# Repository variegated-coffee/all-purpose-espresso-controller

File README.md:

# All Purpose Espresso Controller

Espresso electronics are usually proprietary affairs with little to no expandability. The purpose of this project is to give everyone an open source alternative with lots of features and flexibility. 

It is designed to be useful in many different espresso machines, and for many different hardware configurations. It has the same PCB size as many very common Gicar controllers, making it fairly easy to swap this board into your existing enclosure. It also comes with screw holes, so a 3D printed enclosure is another option.

There's also a [corresponding 100-240 VAC board](https://github.com/open-lcc/all-purpose-espresso-controller-hv-board), with relays and an AC/DC converter, designed to also fit into those same Gicar enclosures.

## High-level features

* RP2040 microcontroller with 2 MB of program flash, and 2 MB of settings flash
* ESP32-S3 for extra processing power and Wi-fi/Bluetooth connectivity
* SD card reader
* Plenty of IO, at 12V, 5V and 3V3 levels
* Dedicated connector for a UART based user interface device, like an [Open LCC](https://github.com/open-lcc/open-lcc-board) or a Nextion touchscreen (selectable 5V or 3V3 level)
* EyeSPI connector for ESP32-S3
* ADS124S08 ADC (intended for e.g. pressure transducers or NTCs)
* FDC1004 Capacitance-to-digital (inteded for e.g. water level probes or capitance based controls)
* QWIIC ports (one per microcontroller) for additional expandability

[IBOM](https://raw.githack.com/open-lcc/all-purpose-espresso-controller/r0d/manufacturing-data/r0d/ibom.html)

## Project status

The current hardware revision is R0D. It hasn't been manufactured yet, and you shouldn't be the first one to do it.

## Disclaimer

Anything you do with this, you do at your own risk. This hardware hasn't even been manufactured by it's creator yet. Your machine uses both line voltage power, high pressured hot water, steam and other dangerous components. You *really* shouldn't be using this yet; in fact, you shouldn't even consider it. Risks include but are not limited to, damaging your machine, personal injury, property damage and summoning dead Cthulhu from his sleep at R'lyeh.

## Connectivity
* CN1 - Display Connector, either for Open LCC or a Nextion Display
  * UART (selectable 3V3 or 5V, default 3V3)
    * JP9 selects voltage
    * RP2040 UART0
    * ESP32 GPIO17/GPIO14
  * 1x 12V output (SR2 DRAIN6)
  * 1x 3V3 output (SR2 DRAIN7)
  * 1 3V3/5V pin and GND pin
* CN2 - HV Board Connector
  * 12V and GND
  * 4 Open drains (SR1 DRAIN0-3)
* CN3 - Separate PSU Connector
  * 12V and GND
* CN4 - Capacitive sense connector
* CN5 - ADC port
  * See note below
* CN6 - ADC port
  * See note below
* CN7 - ADC port
  * See note below
* CN8 - Outputs
  * 4x 5V/12V Outputs
    * Voltage selectable by JP4-6/JP16
  * GND
* CN9 - Open drains and 3V3 IO
  * 3x Open drains (SR1 DRAIN5-7)
  * 3x 3V3 IO (RP2040 GPIO12-14)
  * 12V/GND
* CN10 - Open drain
  * SR2 DRAIN1
  * 12V
* CN11 - Open drain
  * SR2 DRAIN0
  * 12V
* CN12 - 3V3/5V GPIO
  * RP2040 GPIO22
  * Shifted through MOSFET level shifter
  * Can be switched to a 500 mA output with solder jumper
  * GND
* CN13 - 3V3/5V GPIO
  * RP2040 GPIO23
  * Shifted through MOSFET level shifter
  * Can be switched to a 500 mA output with solder jumper
  * GND
* CN14 - GPIO
  * RP2040 GPIO18-21
    * GP19 can be connected to SD Card Detect via a solder jumper
    * GP21 is also connected to an LED
  * RP2040 GPIO26-29
    * ADC Capable

### ADC
By default, CN5 and CN6 are configured for a ratiometric measurement. In order to use it as such, you need to fit a reference resistor for REF0. The reference resistor needs to be larger than the measured values (e.g. for a PT100, use a 400 ohm resistor), and needs to be high accuracy and low drift. 

AIN1-2, AIN4-7, and AIN9-10 are all outfitted with RC filters, as is REF0. The board is also designed in such a way that you can, by sacrificing an RC filter, convert a channel to instead use an upstream resistor divider. 

The ADS124S08 features two external references (REF0 and REF1), as well as an internal 2.5V reference. AIN6-7 double as REFP1/REFN1. The board is designed with footprints for a reference resistor.

#### Common configurations

##### PT100 RTD

##### PT1000 RTD

##### 50k NTC - Ratiometric

##### 50k NTC - Resistor divider

##### 0.3 – 4.5 V Pressure trandducer - 5 V Reference

##### 0.3 – 4.5 V Pressure trandducer - Resistor divider

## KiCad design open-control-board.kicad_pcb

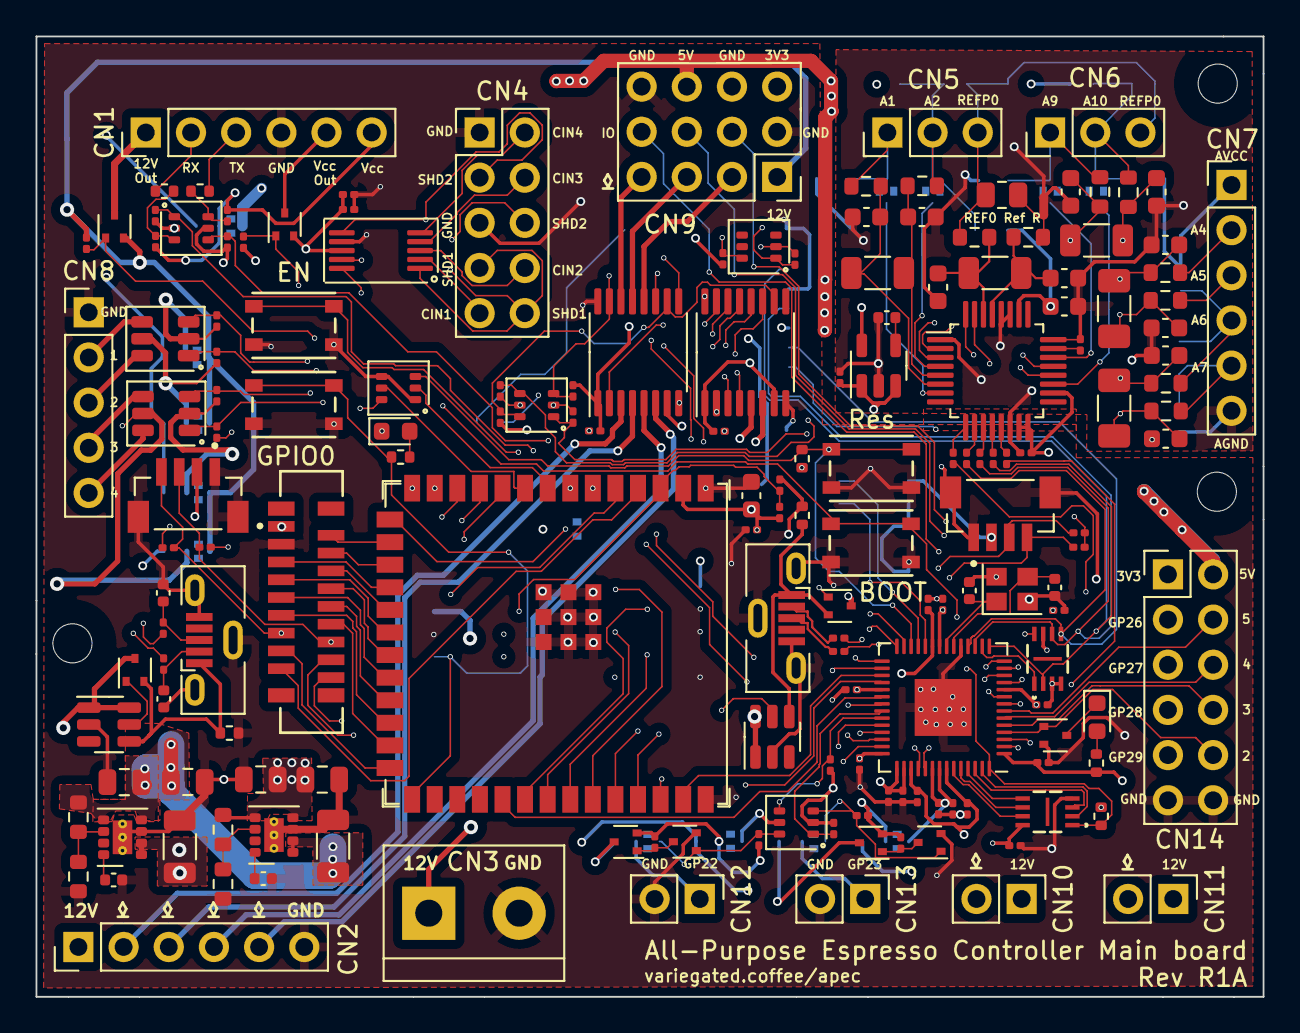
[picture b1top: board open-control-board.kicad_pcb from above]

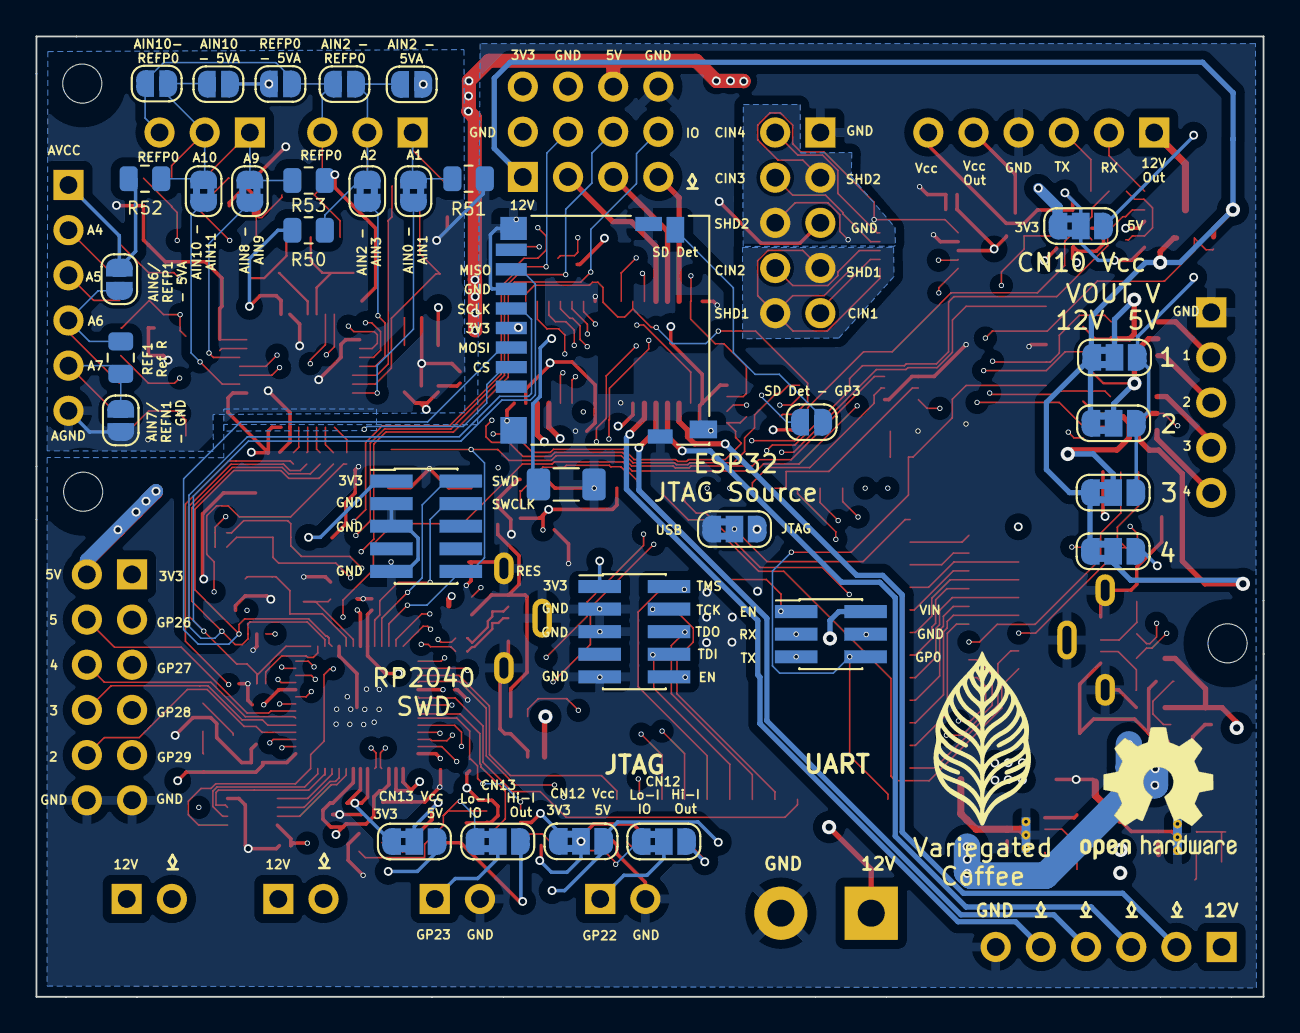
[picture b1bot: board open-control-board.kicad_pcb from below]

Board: 6 copper layers, 69.0 x 54.0 mm, 203 parts (32 on the bottom side), 175 nets.

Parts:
C1, C5, C48: 6.8 nF, 50V; C_0402_1005Metric
C2, C6: 10 μF, 25 V, X7R; C_1206_3216Metric
C3, C28, C36: 51 nF, C0G; C_1206_3216Metric
C4, C8, C49, C50: 22 uF, 10V, X7T; C_0805_2012Metric
C7, C26, C29, C35, C37, C38, C40, C41, C43, C44: 5.1 nF, C0G; C_0603_1608Metric
C9, C10: 12 pF; C_0402_1005Metric
C11, C22, C25, C30, C47, C51: 1 uF, >6.3V, X5R; C_0201_0603Metric
C12, C13, C14, C15, C16, C17, C18, C19, C20, C21, C23, C24, C27, C31, C45, C53, C54: 100 nF, >10V, X6S; C_0201_0603Metric
C32: 22 uF, 6.3V, X5R; C_0603_1608Metric
C33, C34: NC; C_0402_1005Metric
C39, C42: C_Small; C_1206_3216Metric_Pad1.33x1.80mm_HandSolder
C46: 330 nF; C_0603_1608Metric
C52: 47 uF; C_1206_3216Metric_Pad1.33x1.80mm_HandSolder
CN1: LCC Port; PinHeader_1x06_P2.54mm_Vertical
CN2, CN7: Conn_01x06_Pin; PinHeader_1x06_P2.54mm_Vertical
CN3: 12V Separate Supply; TerminalBlock_bornier-2_P5.08mm
CN4: Conn_02x05_Counter_Clockwise; PinHeader_2x05_P2.54mm_Vertical
CN5: NTC Brew Boiler; PinHeader_1x03_P2.54mm_Vertical
CN6: NTC Service Boiler; PinHeader_1x03_P2.54mm_Vertical
CN8: Conn_01x05_Pin; PinHeader_1x05_P2.54mm_Vertical
CN9: Conn_3x04
CN10, CN11, CN12, CN13: PinHeader_1x02_P2.54mm_Vertical
CN14: Conn_02x06_Odd_Even; PinHeader_2x06_P2.54mm_Vertical
D1, D2: KT-0603W; LED_0603_1608Metric
H1, H2, H3: MountingHole; MountingHole_2.2mm_M2
J1, J16: USB_B_Micro; USB_Micro-B_Molex-105133-0001
J2, J17: BM04B-SRSS-TB(LF)(SN); JST_BM04B-SRSS-TB(LF)(SN)
J3: Conn_02x03_Odd_Even; PinHeader_2x03_P1.27mm_Vertical_SMD
J4: Molex_0525591853; CON_525591853_MOL
J5: Micro_SD_Card_Det_Hirose_DM3AT; microSD_HC_Hirose_DM3D-SF
J13, J15: Conn_02x05_Odd_Even; PinHeader_2x05_P1.27mm_Vertical_SMD
JP1, JP2, JP3, JP7, JP10, JP15, JP22, JP23: SolderJumper_2_Open; SolderJumper-2_P1.3mm_Open_RoundedPad1.0x1.5mm
JP4, JP5, JP6, JP8, JP9, JP16, JP18, JP19, JP24, JP25: SolderJumper_3_Bridged12; SolderJumper-3_P1.3mm_Bridged2Bar12_RoundedPad1.0x1.5mm_Num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
JP13, JP17, JP20, JP21: SolderJumper_2_Bridged; SolderJumper-2_P1.3mm_Bridged2Bar_RoundedPad1.0x1.5mm
NT1: NetTie_2; NetTie-2_SMD_Pad0.5mm
Q1, Q2, Q8, Q15: DMP21D0UT-7; SOT-523
Q3, Q5: Q_PMOS-E_DUAL_Generic_SEP_S1G1D2S2G2D1; TSOT-23-6
Q4, Q6, Q7, Q11, Q12: DMN63D8LDW; SOT-363_SC-70-6
Q9, Q10, Q13, Q14, Q16: DMG1012T-7; SOT-523
R1, R2, R19, R22, R23, R28, R29, R30, R34, R36, R37, R38, R39, R40, R41, R42, R43, R59, R61, R62, R63, R64, R65, R67, R68, R69, R70: 10K; R_0201_0603Metric
R3, R13: 18K7; R_0402_1005Metric
R4, R50, R51, R52, R53, R66: R_Small; R_0805_2012Metric
R5, R6: 1K; R_0402_1005Metric
R7: 71K5; R_0603_1608Metric
R8: 13K3; R_0603_1608Metric
R9: 75K; R_0603_1608Metric
R10: 24K; R_0603_1608Metric
R11, R12: 27R; R_0201_0603Metric
R14, R15, R21, R24, R25, R26, R27, R35: 6K04 1%; R_0603_1608Metric
R16, R20: 4K99 1%; R_0603_1608Metric
R17, R18: 4K7; R_0402_1005Metric
R31, R44: 120R; R_0402_1005Metric
R32, R33: 0R; R_0201_0603Metric
R45, R46, R47, R48, R49: 47R; R_0201_0603Metric
SW1, SW2, SW3, SW4: SW_Push; SW4_PTS815 SJM 250 SMTR LFS_CNK
U1, U3: TPS82130; Texas_SIL0008D_MicroSiP-8-1EP_2.8x3mm_P0.65mm_EP1.1x1.9mm_T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
U2, U9: W25Q16JVUXIQ; W25Q16JVUXIQ_WIN
U4: RP2040; QFN-56-1EP_7x7mm_P0.4mm_EP3.2x3.2mm
U5: ESP32-S3-WROOM-1; ESP32-S3-WROOM-1U
U6: ADS124S08IPBSR; LQFP-32_5x5mm_P0.5mm
U7, U8: LM5050-1; TSOT-23-6
U10: FDC1004; VSSOP-10_3x3mm_P0.5mm
U11: TC2014-5.0VxCTTR; SOT-23-5
U15, U16: STPIC6C595TTR; TSSOP-16_4.4x5mm_P0.65mm
Y1: XYDBPCNANF-12MHZ; Crystal_SMD_2520-4Pin_2.5x2.0mm

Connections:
+3V3: C8.1, C14.2, C15.2, C16.2, C17.2, C18.2, C19.2, C20.1, C21.1, C22.1, C23.2, C24.1, C25.1, C27.2, C31.2, C32.2, C45.1, C50.1, C52.1, CN9.9, CN14.1, J2.2, J4.1 (Vcc), J5.4 (VDD), J13.1, J15.1, J17.2, JP8.3 (B), JP9.1 (A), JP19.1 (A), JP24.1 (A), Q1.2 (S), Q4.2 (G1), Q4.5 (G2), Q6.2 (G1), Q11.2 (G1), Q11.5 (G2), Q12.2 (G1), Q12.5 (G2), R1.1, R9.1, R17.2, R18.2, R22.2, R23.1, R34.1, R36.2, R37.1, R38.1, R40.1, R42.1, R44.1, R61.1, R62.1, R65.1, R67.1, U2.8 (VCC), U3.4 (VOUT), U3.5 (VOUT), U4.1 (IOVDD), U4.10 (IOVDD), U4.22 (IOVDD), U4.33 (IOVDD), U4.42 (IOVDD), U4.43 (ADC_AVDD), U4.44 (VREG_IN), U4.48 (USB_VDD), U4.49 (IOVDD), U5.2 (3V3), U6.15 (IOVDD), U6.16 (DVDD), U6.18 (RESET_N), U9.8 (VCC), U10.8 (VDD)
+5V: C4.1, C6.2, C49.1, C51.1, C53.2, C54.2, CN9.11, CN14.2, JP4.3 (B), JP5.3 (B), JP6.3 (B), JP9.3 (B), JP16.3 (B), JP19.3 (B), JP24.3 (B), R7.1, R39.1, R41.1, R43.1, U1.4 (VOUT), U1.5 (VOUT), U3.1 (EN), U3.2 (VIN), U11.1 (VIN), U11.3 (ON/~OFF), U15.1 (VCC), U15.7 (~CLR), U16.1 (VCC), U16.7 (~CLR)
+5VA: C46.1, CN7.1, JP1.1 (A), JP2.1 (A), JP7.1 (A), JP10.1 (A), R50.2, R52.2, U6.26 (AVDD), U11.5 (VOUT)
/RP2040_USB_POST_R_DN: J1.2 (D-), R12.1
/RP2040_USB_POST_R_DP: J1.3 (D+), R11.1
ADC_CS: R49.2, U4.2 (GPIO0)
ADC_DRDY: R45.2, U4.35 (GPIO23)
AIN0: JP13.2 (B), U6.7 (AIN0)
AIN1: C3.2, C7.1, R14.2, U6.6 (AIN1)
AIN1_COND: CN5.1, JP13.1 (A), R14.1, R51.1
AIN2: C3.1, C26.2, R15.1, U6.5 (AIN2)
AIN2_COND: CN5.2, JP7.2 (B), JP17.2 (B), JP23.2 (B), R15.2, R50.1
AIN3: JP17.1 (A), U6.4 (AIN3)
AIN4: C42.2, C43.1, R27.2, U6.3 (AIN4)
AIN4_COND: CN7.2, R27.1
AIN5: C42.1, C44.2, R35.1, U6.2 (AIN5)
AIN5_COND: CN7.3, R35.2
AIN6_REFP1: C39.2, C40.1, R25.2, U6.32 (REFP1_AIN6)
AIN6_REFP1_COND: CN7.4, JP2.2 (B), R25.1, R66.1
AIN7_REFN1: C39.1, C41.2, R26.1, U6.31 (REFN1_AIN7)
AIN7_REFN1_COND: CN7.5, JP3.2 (B), R26.2, R66.2
AIN8: JP20.2 (B), U6.22 (GPIO0_AIN8)
AIN9: C36.2, C37.1, R21.2, U6.21 (GPIO1_AIN9)
AIN9_COND: CN6.1, JP20.1 (A), R21.1, R53.1
AIN10: C36.1, C38.2, R24.1, U6.20 (GPIO2_AIN10)
AIN10_COND: CN6.2, JP10.2 (B), JP21.2 (B), JP22.2 (B), R24.2, R52.1
AIN11: JP21.1 (A), U6.19 (GPIO3_AIN11)
CIN1: CN4.9, U10.2 (CIN1)
CIN2: CN4.8, U10.3 (CIN2)
CIN3: CN4.4, U10.4 (CIN3)
CIN4: CN4.2, U10.5 (CIN4)
CN1_3V3_GATE: Q1.1 (G), R1.2, U16.14 (DRAIN7)
CN1_12V_GATE: Q2.1 (G), R2.1, U16.13 (DRAIN6)
CN1_UART_RX: Q11.3 (D2), R5.2, R64.2
CN1_UART_RX_SHIFT_SEL: Q11.4 (S2), R65.2, U4.28 (GPIO17), U5.7 (GPIO7/TOUCH7/ADC1_CH6)
CN1_UART_TX: Q11.1 (S1), R62.2, U4.27 (GPIO16), U5.6 (GPIO6/TOUCH6/ADC1_CH5)
CN1_UART_TX_SHIFT_SEL: Q11.6 (D1), R6.2, R63.2
CN1_UART_VCC: CN1.6, JP9.2 (C), R63.1, R64.1
CN2_FA7: CN2.5, U15.6 (DRAIN3)
CN2_FA8: CN2.4, U15.5 (DRAIN2)
CN2_FA9: CN2.3, U15.4 (DRAIN1)
CN2_FA10: CN2.2, U15.3 (DRAIN0)
CN9_3: CN9.3, U15.12 (DRAIN5)
CN9_4: CN9.4, U4.12 (GPIO9)
CN9_5: CN9.5, U15.13 (DRAIN6)
CN9_6: CN9.6, U4.13 (GPIO10)
CN9_7: CN9.7, U15.14 (DRAIN7)
CN9_8: CN9.8, U4.14 (GPIO11)
CN10_DRAIN: CN10.2, U16.5 (DRAIN2)
CN11_DRAIN: CN11.2, U16.6 (DRAIN3)
CN12: CN12.1, JP25.2 (C)
CN12_3V3: Q12.1 (S1), R61.2, U4.36 (GPIO24)
CN12_HighI: JP25.3 (B), Q8.3 (D)
CN12_LowI: JP25.1 (A), Q9.1 (G), Q12.6 (D1), R68.2
CN12_VCC: JP19.2 (C), Q8.2 (S), R68.1, R70.2
CN13: CN13.1, JP18.2 (C)
CN13_3V3: Q12.4 (S2), R67.2, U4.37 (GPIO25)
CN13_HighI: JP18.3 (B), Q15.3 (D)
CN13_LowI: JP18.1 (A), Q10.1 (G), Q12.3 (D2), R69.2
CN13_VCC: JP24.2 (C), Q15.2 (S), R59.2, R69.1
CN14_3: CN14.3, U4.38 (GPIO26_ADC0)
CN14_4: CN14.4, U4.7 (GPIO5)
CN14_5: CN14.5, U4.39 (GPIO27_ADC1)
CN14_6: CN14.6, U4.6 (GPIO4)
CN14_7: CN14.7, U4.40 (GPIO28_ADC2)
CN14_8: CN14.8, JP15.1 (A), U4.5 (GPIO3)
CN14_9: CN14.9, U4.41 (GPIO29_ADC3)
CN14_10: CN14.10, Q16.1 (G), U4.4 (GPIO2)
C_SHIELD_1: CN4.7, CN4.10, U10.1 (SHLD1)
C_SHIELD_2: CN4.3, CN4.6, U10.6 (SHLD2)
ESP32_BOOTSEL_RP2040: Q7.2 (G1), U5.8 (GPIO15/U0RTS/ADC2_CH4/XTAL_32K_P)
ESP32_DISABLE_RP2040: Q7.5 (G2), U5.9 (GPIO16/U0CTS/ADC2_CH5/XTAL_32K_N)
ESP32_EN: C30.2, J3.1, J15.10, R34.2, SW4.1, U5.3 (EN)
ESP32_GPIO0: J3.6, R31.1, SW3.1, U5.27 (GPIO0/BOOT)
ESP32_JTAG_SELECT: JP8.2 (C), U5.15 (GPIO3/TOUCH3/ADC1_CH2)
ESP32_QWIIC_SCL: J4.13 (SCL), J17.4, R36.1, U5.12 (GPIO8/TOUCH8/ADC1_CH7/SUBSPICS1)
ESP32_QWIIC_SDA: J4.14 (SDA), J17.3, R37.2, U5.11 (GPIO18/U1RXD/ADC2_CH7/CLK_OUT3)
ESP32_RP2040_UART1: U4.31 (GPIO20), U5.39 (GPIO1/TOUCH1/ADC1_CH0)
ESP32_RP2040_UART2: U4.32 (GPIO21), U5.38 (GPIO2/TOUCH2/ADC1_CH1)
ESP32_TCK: J15.4, U5.32 (MTCK/GPIO39/CLK_OUT3/SUBSPICS1)
ESP32_TDI: J15.8, U5.34 (MTDI/GPIO41/CLK_OUT1)
ESP32_TDO: J15.6, U5.33 (MTDO/GPIO40/CLK_OUT2)
ESP32_TMS: J15.2, U5.35 (MTMS/GPIO42)
ESP32_U0RXD: J3.5, U5.36 (U0RXD/GPIO44/CLK_OUT2)
ESP32_U0TXD: J3.3, U5.37 (U0TXD/GPIO43/CLK_OUT1)
ESP32_USB_PRE_R_DN: R33.2, U5.13 (GPIO19/U1RTS/ADC2_CH8/CLK_OUT2/USB_D-)
ESP32_USB_PRE_R_DP: R32.2, U5.14 (GPIO20/U1CTS/ADC2_CH9/CLK_OUT1/USB_D+)
ESP32_USB_VBUS: J16.1 (VBUS), Q13.2 (S), R3.1, U7.4 (IN)
EYESPI_BL: J4.2 (BACKLIGHT), U5.16 (GPIO46)
EYESPI_BUSY_TE: J4.16 (BUSY/TE), U5.10 (GPIO17/U1TXD/ADC2_CH6)
EYESPI_DC: J4.7 (DC), U5.20 (GPIO12/TOUCH12/ADC2_CH1/FSPICLK/FSPIIO6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)
EYESPI_DISP_CS: J4.9 (DISP_CS), U5.22 (GPIO14/TOUCH14/ADC2_CH3/FSPIWP/FSPIDQS/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)
EYESPI_GPIO1: J4.17 (GPIO1), U5.4 (GPIO4/TOUCH4/ADC1_CH3)
EYESPI_GPIO2: J4.18 (GPIO2), U5.5 (GPIO5/TOUCH5/ADC1_CH4)
EYESPI_INT: J4.15 (INT), U5.26 (GPIO45)
EYESPI_MEM_CS: J4.11 (MEM_CS), U5.24 (GPIO47/SPICLK_P/SUBSPICLK_P_DIFF)
EYESPI_MISO: J4.6 (MISO), U5.19 (GPIO11/TOUCH11/ADC2_CH0/FSPID/FSPIIO5/S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)
EYESPI_MOSI: J4.5 (MOSI), U5.18 (GPIO10/TOUCH10/ADC1_CH9/FSPICS0/FSPIIO4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)
EYESPI_RESET: J4.8 (RESET), U5.21 (GPIO13/TOUCH13/ADC2_CH2/FSPIQ/FSPIIO7/S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)
EYESPI_SCK: J4.4 (SCK), U5.17 (GPIO9/TOUCH9/ADC1_CH8/FSPIHD/SUBSPIHD)
EYESPI_SD_CS: J4.10 (SD_CS), U5.23 (GPIO21)
EYESPI_TS_CS: J4.12 (TS_CS), U5.25 (GPIO48/SPICLK_N/SUBSPICLK_N_DIFF)
GND: C1.2, C2.1, C4.2, C5.2, C6.1, C7.2, C8.2, C9.2, C10.2, C11.2, C12.2, C13.2, C14.1, C15.1, C16.1, C17.1, C18.1, C19.1, C20.2, C21.2, C22.2, C23.1, C24.2, C25.2, C26.1, C27.1, C29.2, C30.1, C31.1, C32.1, C33.1, C34.2, C35.1, C37.2, C38.1, C40.2, C41.1, C43.2, C44.1, C45.2, C46.2, C47.2, C48.2, C49.2, C50.2, C51.2, C52.2, C53.1, C54.1, CN1.4, CN2.6, CN3.2, CN4.1, CN4.5, CN7.6, CN8.1, CN9.2, CN9.10, CN9.12, CN12.2, CN13.2, CN14.11, CN14.12, D2.1 (K), J1.5 (GND), J1.6 (Shield), J2.1, J2.S1 (SHIELD), J2.S2 (SHIELD), J3.4, J4.3 (GND), J5.6 (VSS), J5.10 (DET_A), J5.11 (SHIELD), J13.3, J13.5, J13.9, J15.3, J15.5, J15.9, J16.5 (GND), J16.6 (Shield), J17.1, J17.S1 (SHIELD), J17.S2 (SHIELD), JP3.1 (A), JP8.1 (A), NT1.1, Q7.1 (S1), Q7.4 (S2), Q9.2 (S), Q10.2 (S), Q16.2 (S), R3.2, R8.1, R10.1, R13.2, R51.2, R53.2, SW1.2, SW2.2, SW3.2, SW4.2, U1.3 (GND), U1.9 (GND), U2.3 (~WP/IO2), U2.4 (GND), U2.7 (~HOLD/IO3), U3.3 (GND), U3.9 (GND), U4.19 (TESTEN), U4.57 (GND), U5.1 (GND), U5.40 (GND), U5.41 (GND), U6.1 (AINCOM), U6.14 (DGND), U6.24 (REFCOM), U6.27 (AVSS), U6.28 (AVSS), U7.2 (GND), U8.2 (GND), U9.4 (GND), U10.7 (GND), U11.2 (GND), U15.8 (~G), U15.16 (GND), U16.8 (~G), U16.16 (GND), Y1.2, Y1.4
INT_SPI_MISO: J5.7 (DAT0), R46.2, U2.2 (SO/IO1), U4.15 (GPIO12)
INT_SPI_MOSI: J5.3 (CMD), R48.2, U2.5 (SI/IO0), U4.18 (GPIO15)
INT_SPI_SCLK: J5.5 (CLK), R47.2, U2.6 (SCK), U4.17 (GPIO14)
unnamed: CN1.1, Q2.3 (D)
unnamed: CN1.2, R5.1
unnamed: CN1.3, R6.1
unnamed: CN1.5, Q1.3 (D)
unnamed: D1.2 (A), R44.2
unnamed: D1.1 (K), Q16.3 (D)
unnamed: D2.2 (A), R31.2
unnamed: C33.2, J16.3 (D+), R32.1
unnamed: C34.1, J16.2 (D-), R33.1
unnamed: JP4.2 (C), Q5.2 (S2), R28.1
unnamed: JP5.2 (C), Q5.5 (S1), R29.1
unnamed: JP6.2 (C), Q3.2 (S2), R30.1
unnamed: JP16.2 (C), Q3.5 (S1), R19.1
unnamed: NT1.2, R4.2, R20.2
unnamed: Q8.1 (G), Q9.3 (D), R70.1
unnamed: Q10.3 (D), Q15.1 (G), R59.1
unnamed: Q13.1 (G), U7.5 (GATE)
unnamed: Q14.1 (G), U8.5 (GATE)
unnamed: R7.2, R8.2, U1.6 (FB)
unnamed: C1.1, U1.8 (SS/TR)
unnamed: R9.2, R10.2, U3.6 (FB)
unnamed: C5.1, U3.8 (SS/TR)
unnamed: C11.1, C12.1, C13.1, U4.23 (DVDD), U4.45 (VREG_VOUT), U4.50 (DVDD)
unnamed: C9.1, U4.20 (XIN), Y1.3
unnamed: C10.1, U4.21 (XOUT), Y1.1
unnamed: R49.1, U6.9 (CS_N)
unnamed: R48.1, U6.10 (DIN)
unnamed: R46.1, U6.12 (DOUT_DRDY_N)
unnamed: R45.1, U6.13 (DRDY_N)
unnamed: C47.1, U6.23 (REFOUT)
unnamed: R47.1, U6.11 (SCLK)
unnamed: C48.1, U11.4 (BP)
unnamed: U15.9 (SER_OUT), U16.2 (SER_IN)
QWIIC_SCL: J2.4, R22.1, U4.30 (GPIO19), U10.9 (SCL)
QWIIC_SDA: J2.3, R23.2, U4.29 (GPIO18), U10.10 (SDA), U15.11 (DRAIN4)
RCLK_3V3: Q4.1 (S1), R38.2, U4.9 (GPIO7)
RCLK_5V: Q4.6 (D1), R39.2, U15.10 (RCK), U16.10 (RCK)
REFN0: C28.1, C35.2, R20.1, U6.29 (REFN0)
REFP0: C28.2, C29.1, R16.2, U6.30 (REFP0)
REF_IN: CN5.3, CN6.3, JP1.2 (B), JP22.1 (A), JP23.1 (A), R4.1, R16.1
RP2040_BOOTSEL: Q7.6 (D1), R17.1, SW1.1, U4.56 (QSPI_SS), U9.1 (~CS)
RP2040_QSPI_SCK: U4.52 (QSPI_SCLK), U9.6 (SCK)
RP2040_QSPI_SD0: U4.53 (QSPI_SD0), U9.5 (SI/IO0)
RP2040_QSPI_SD1: U4.55 (QSPI_SD1), U9.2 (SO/IO1)
RP2040_QSPI_SD2: U4.54 (QSPI_SD2), U9.3 (~WP/IO2)
RP2040_QSPI_SD3: U4.51 (QSPI_SD3), U9.7 (~HOLD/IO3)
RP2040_RESETn: J13.10, Q7.3 (D2), R18.1, SW2.1, U4.26 (RUN)
RP2040_SERIAL_BOOT: U4.34 (GPIO22), U5.31 (GPIO38/FSPIWP/SUBSPIWP)
RP2040_SWCLK: J13.4, U4.24 (SWCLK)
RP2040_SWD: J13.2, U4.25 (SWD)
RP2040_USB_PRE_R_DN: R12.2, U4.46 (USB_DM)
RP2040_USB_PRE_R_DP: R11.2, U4.47 (USB_DP)
RP2040_USB_VBUS: J1.1 (VBUS), Q14.2 (S), R13.1, U8.4 (IN)
SD_CS: J5.2 (DAT3/CD), U4.3 (GPIO1)
SD_DET: J5.9 (DET_B), JP15.2 (B)
SER_IN_3V3: Q6.1 (S1), R42.2, U4.8 (GPIO6)
SER_IN_5V: Q6.6 (D1), R43.2, U15.2 (SER_IN)
SET_FLSH_CS: U2.1 (~CS), U4.16 (GPIO13)
SRCK_3V3: Q4.4 (S2), R40.2, U4.11 (GPIO8)
SRCK_5V: Q4.3 (D2), R41.2, U15.15 (SRCK), U16.15 (SRCK)
VIN: C2.2, CN2.1, CN3.1, CN9.1, CN10.1, CN11.1, J3.2, JP4.1 (A), JP5.1 (A), JP6.1 (A), JP16.1 (A), Q2.2 (S), Q13.3 (D), Q14.3 (D), R2.2, U1.1 (EN), U1.2 (VIN), U7.1 (VS), U7.6 (OUT), U8.1 (VS), U8.6 (OUT)
VOUT_1: CN8.2, Q5.4 (D2)
VOUT_1_GATE: Q5.3 (G2), R28.2, U16.12 (DRAIN5)
VOUT_2: CN8.3, Q5.6 (D1)
VOUT_2_GATE: Q5.1 (G1), R29.2, U16.11 (DRAIN4)
VOUT_3: CN8.4, Q3.4 (D2)
VOUT_3_GATE: Q3.3 (G2), R30.2, U16.4 (DRAIN1)
VOUT_4: CN8.5, Q3.6 (D1)
VOUT_4_GATE: Q3.1 (G1), R19.2, U16.3 (DRAIN0)

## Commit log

2024-02-12 Added possibility to select CN10 levels via solder jumpers
2024-02-22 Cheaper resistors
2024-02-24 Split HV board into separate project
2024-02-24 Updated project symbols and footprints
2024-02-24 Clean up schematic and create PDF
2024-02-24 Add License
2024-02-24 Added OSHW logo
2024-03-10 Tag R0A
2024-03-19 R0B changes (WIP)
2024-03-19 Updated schematic
2024-03-19 Add ibom and updated schematic PDF
2024-03-19 Renamed connectors and added a lot of silk screen
2024-03-20 Updated PCB with screw holes
2024-03-20 Changed mounting holes to M2 (to match HV board) and use actual footprints
2024-03-23 Fixes
2024-03-24 Added optional 5V level shifting for CN12-13
2024-03-24 Add DRC Exclusions
2024-03-26 Added test points for unused IO
2024-03-26 Minor updates
2024-03-29 Added preliminary gerbers for r0b
2024-03-29 Removed C43 and C44 from BOM and CPL (these are optional, and only for when ADC2 A0-A1 or A2-A3 are used in differential mode).
    Fixed issue with ADC1 A1 and A3 not being as flexible as they could be. A3 can now properly be untied from CN6, and A1 can either be untied, tied to CN5, or tied to AVCC.
2024-03-29 Moved a few components to get a little more clearance for hand-soldering the ESP32-S3
2024-03-30 Switched JP20 to round footprint.
    Removed a bunch of components that’s not supposed to be in the BOM from the Schematic BOM
2024-03-30 Updated Gerbers and ibom
2024-03-31 Files as sent to manufacturing
2024-03-31 Added notes about manufacturing R0B
2024-04-13 Added errata to R0B readme
2024-04-16 Fix silk screen and flipped FET
2024-04-25 WIP on no TXS
2024-05-11 Fairly finalized design
2024-05-12 Moved USB connector
2024-05-13 Re-added LED and fixed silk screen
2024-05-13 Updated docs
2024-05-13 Updated capacitor footprint
2024-05-16 Added more power connectors to CN9
2024-05-17 Cleaned up schematic
2024-05-29 Added some additional bypass caps for good measure
2024-05-29 Removed stray reference
2024-05-29 Added Variegated Coffee logo and URL
2024-06-10 Final updates (as sent to manufacturer)
2024-07-03 Errata fixes
